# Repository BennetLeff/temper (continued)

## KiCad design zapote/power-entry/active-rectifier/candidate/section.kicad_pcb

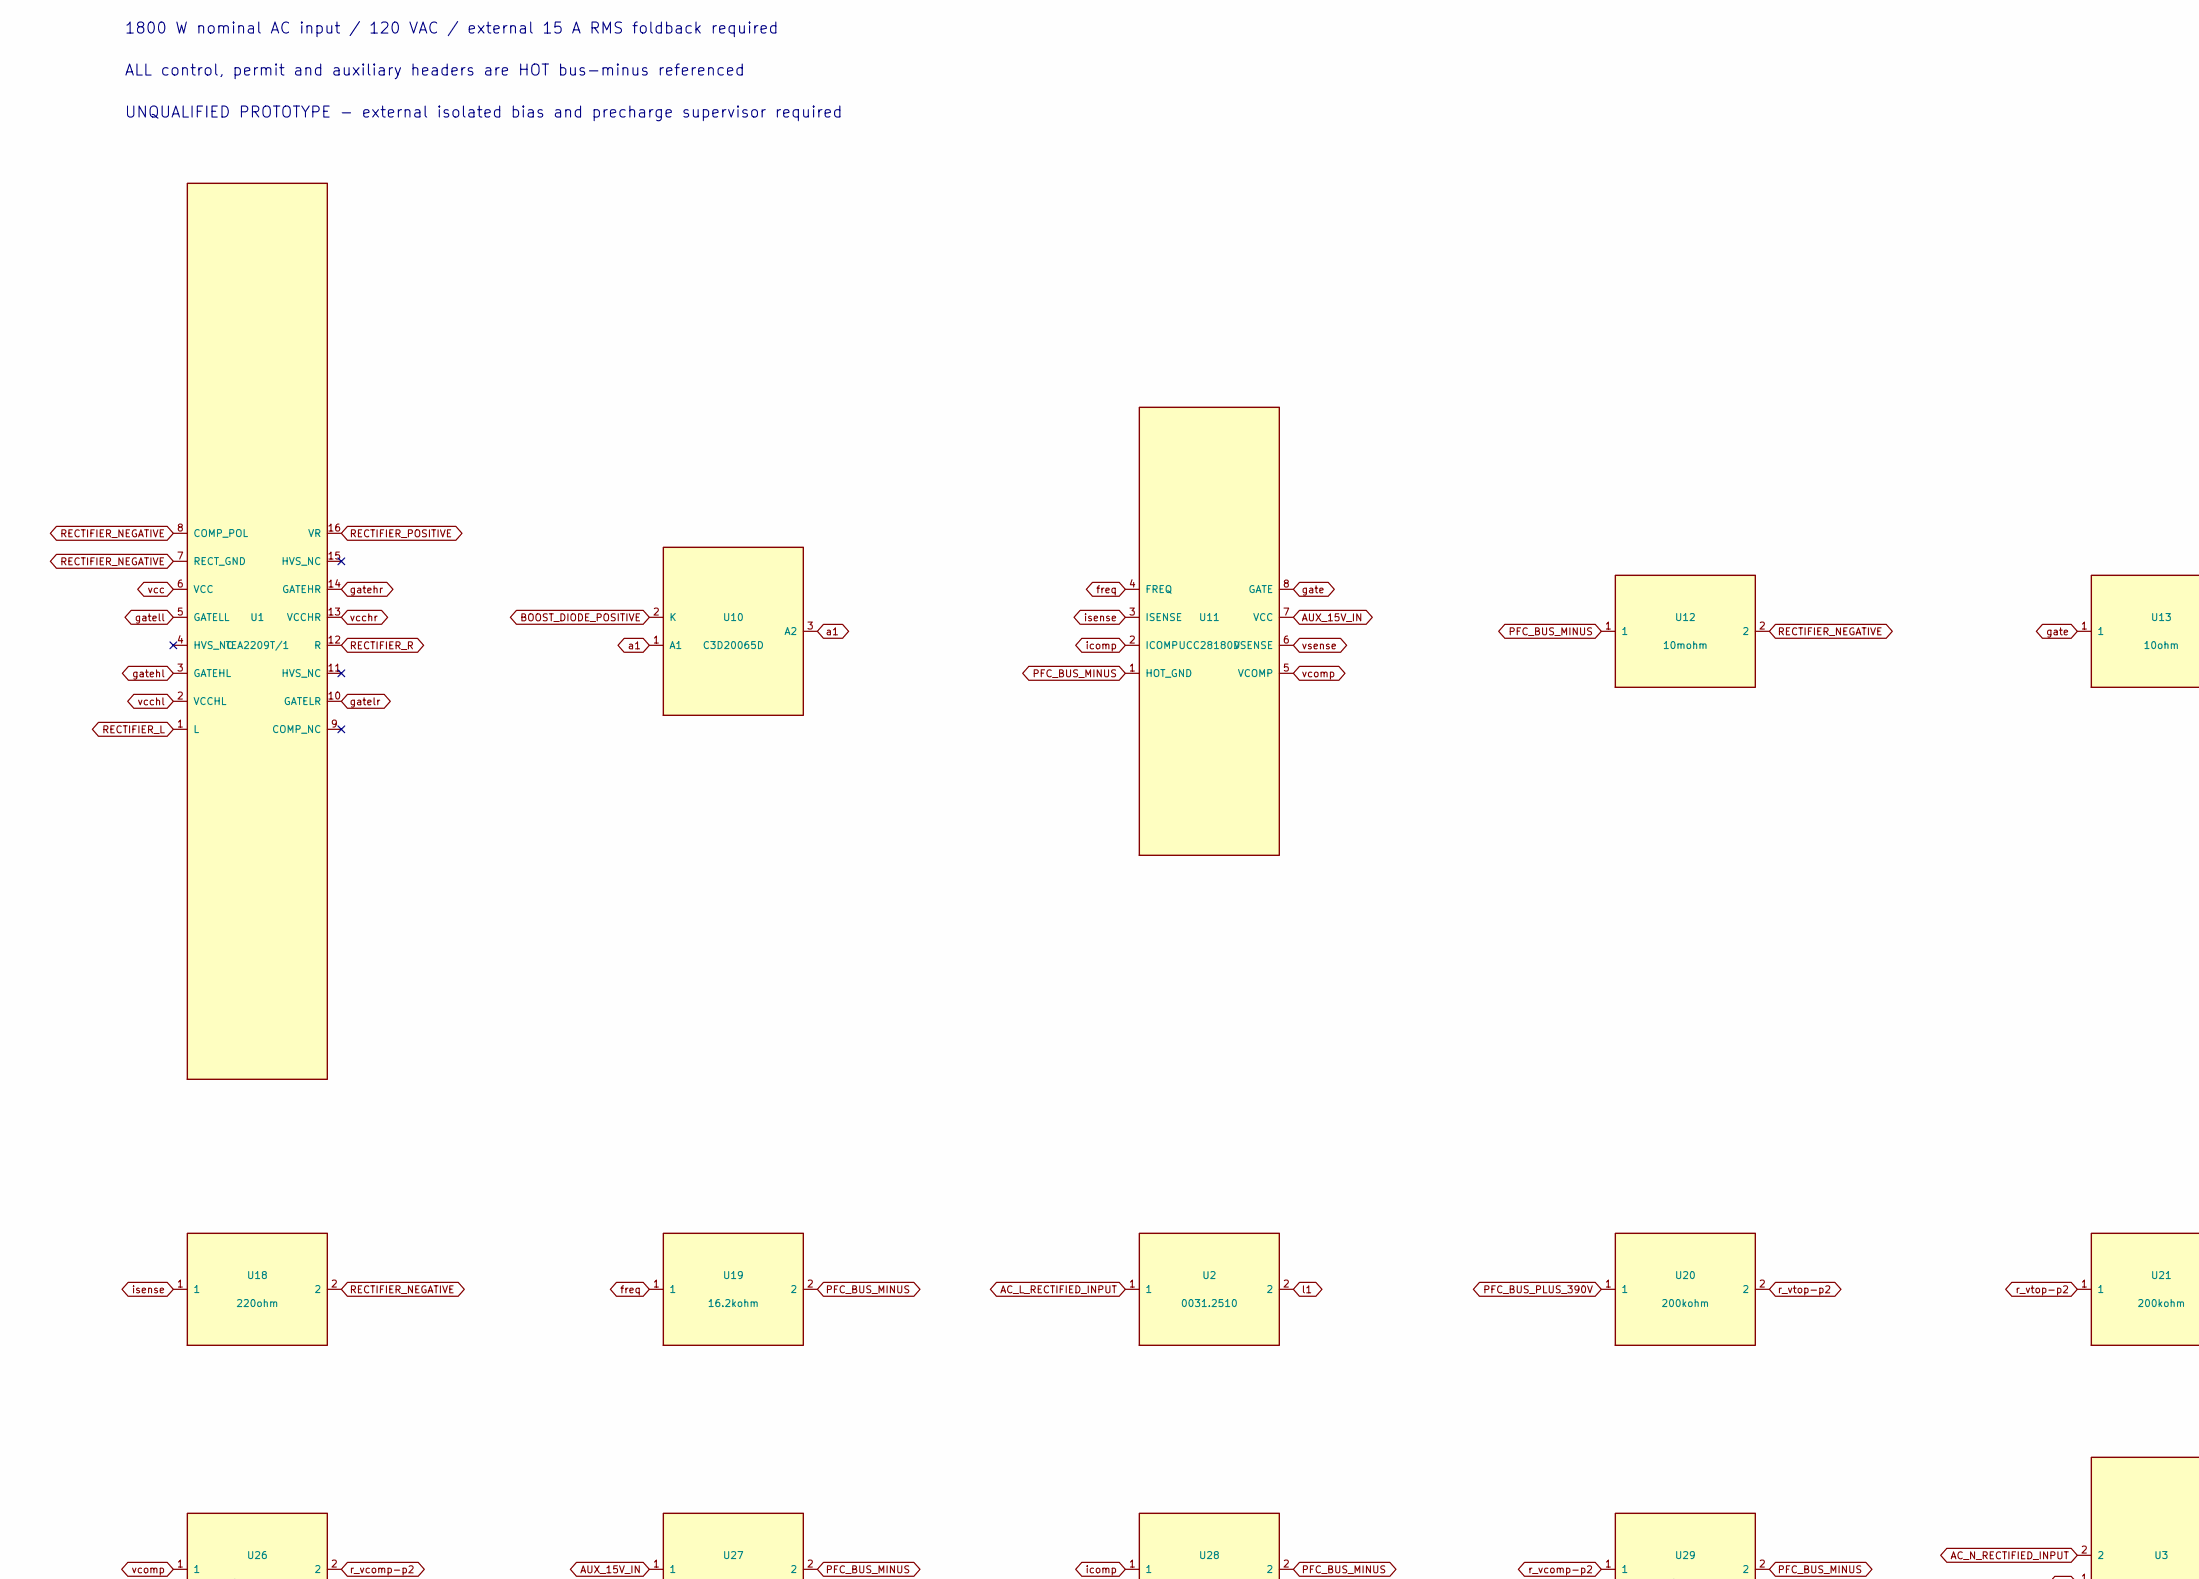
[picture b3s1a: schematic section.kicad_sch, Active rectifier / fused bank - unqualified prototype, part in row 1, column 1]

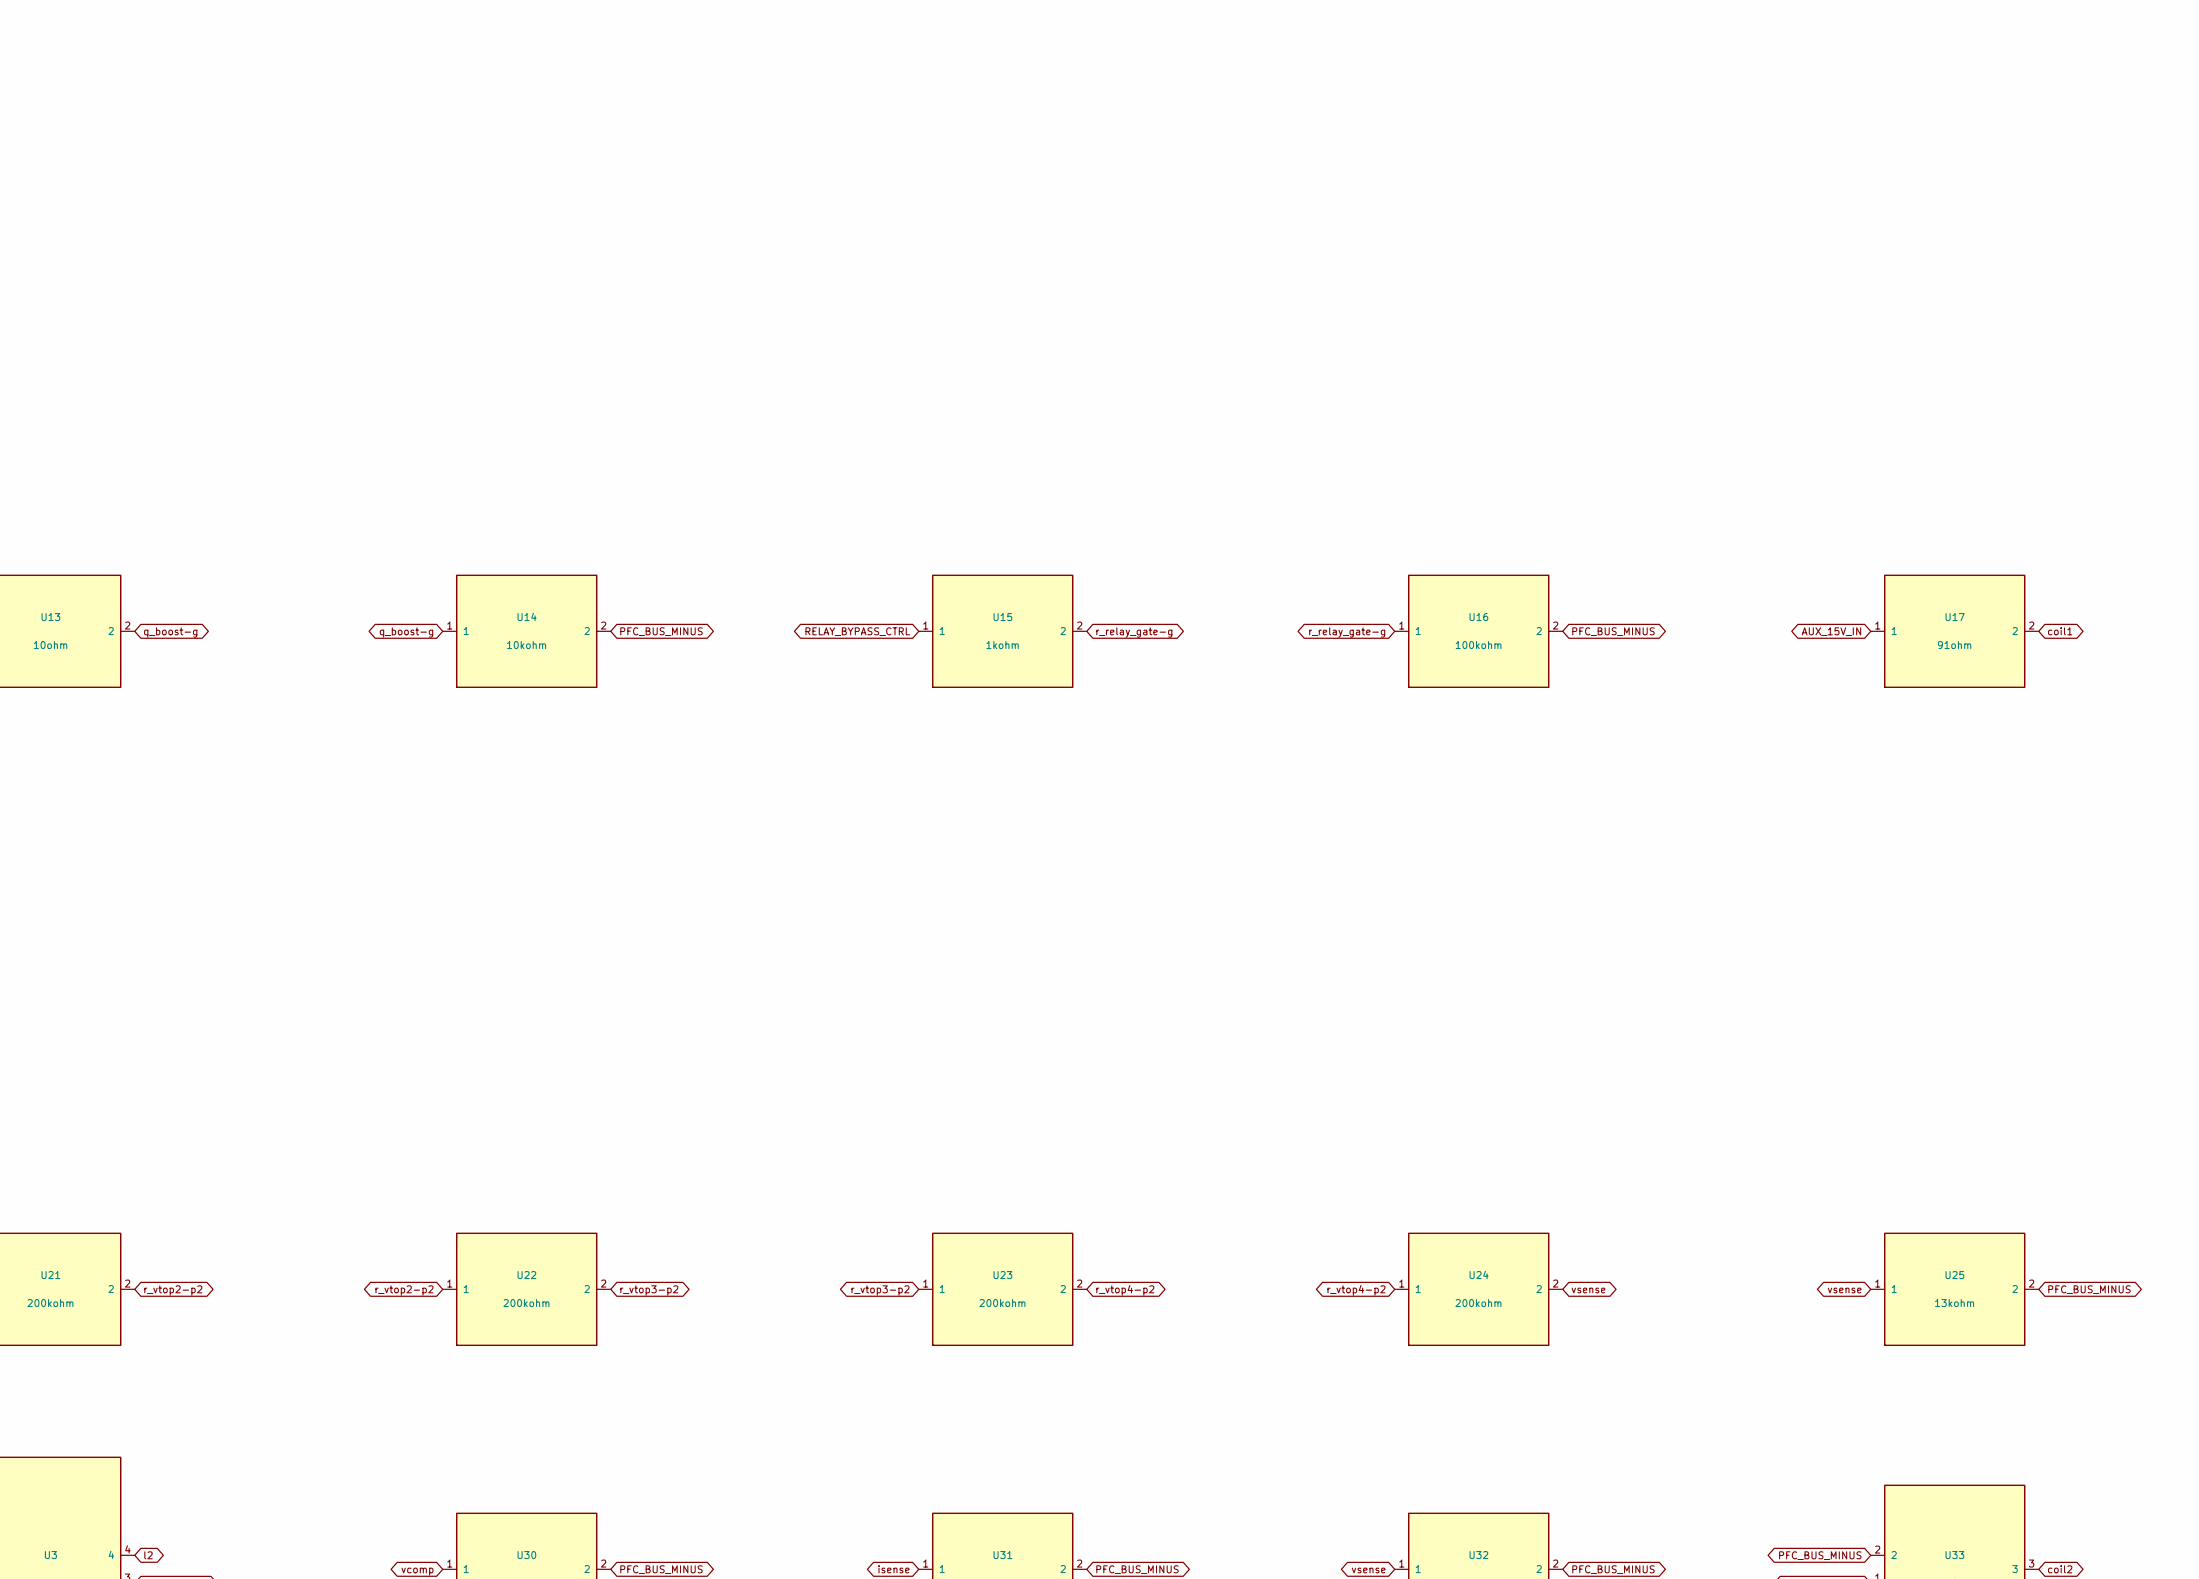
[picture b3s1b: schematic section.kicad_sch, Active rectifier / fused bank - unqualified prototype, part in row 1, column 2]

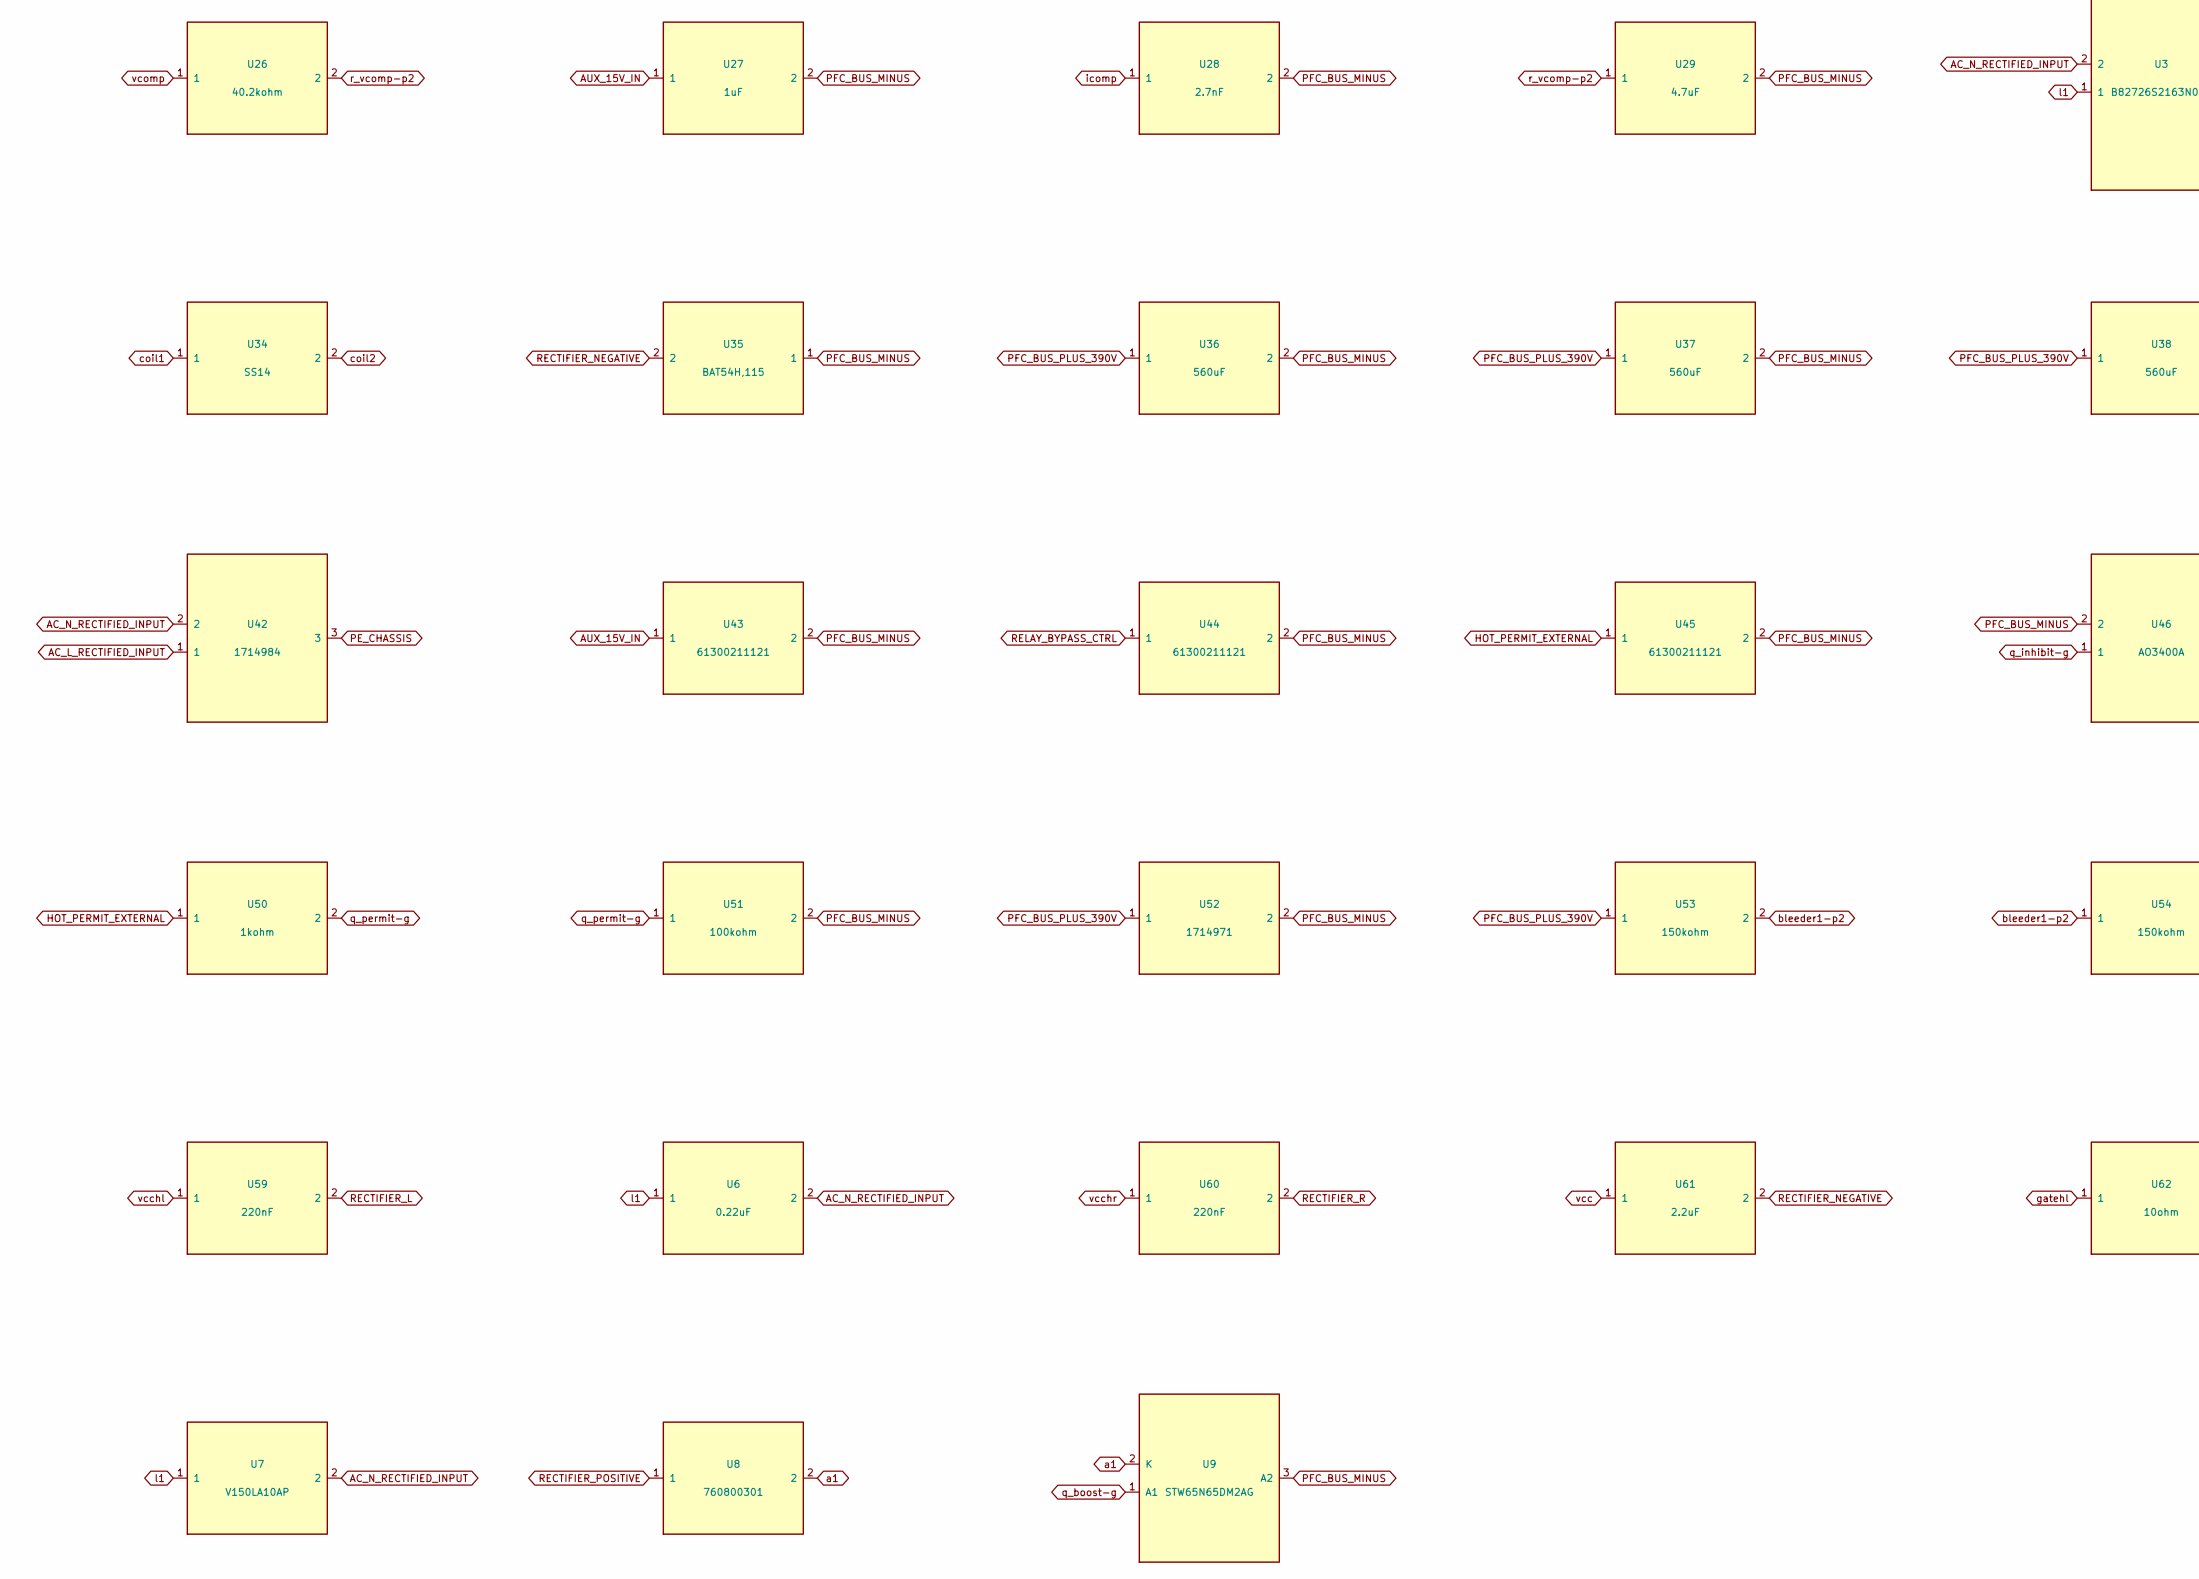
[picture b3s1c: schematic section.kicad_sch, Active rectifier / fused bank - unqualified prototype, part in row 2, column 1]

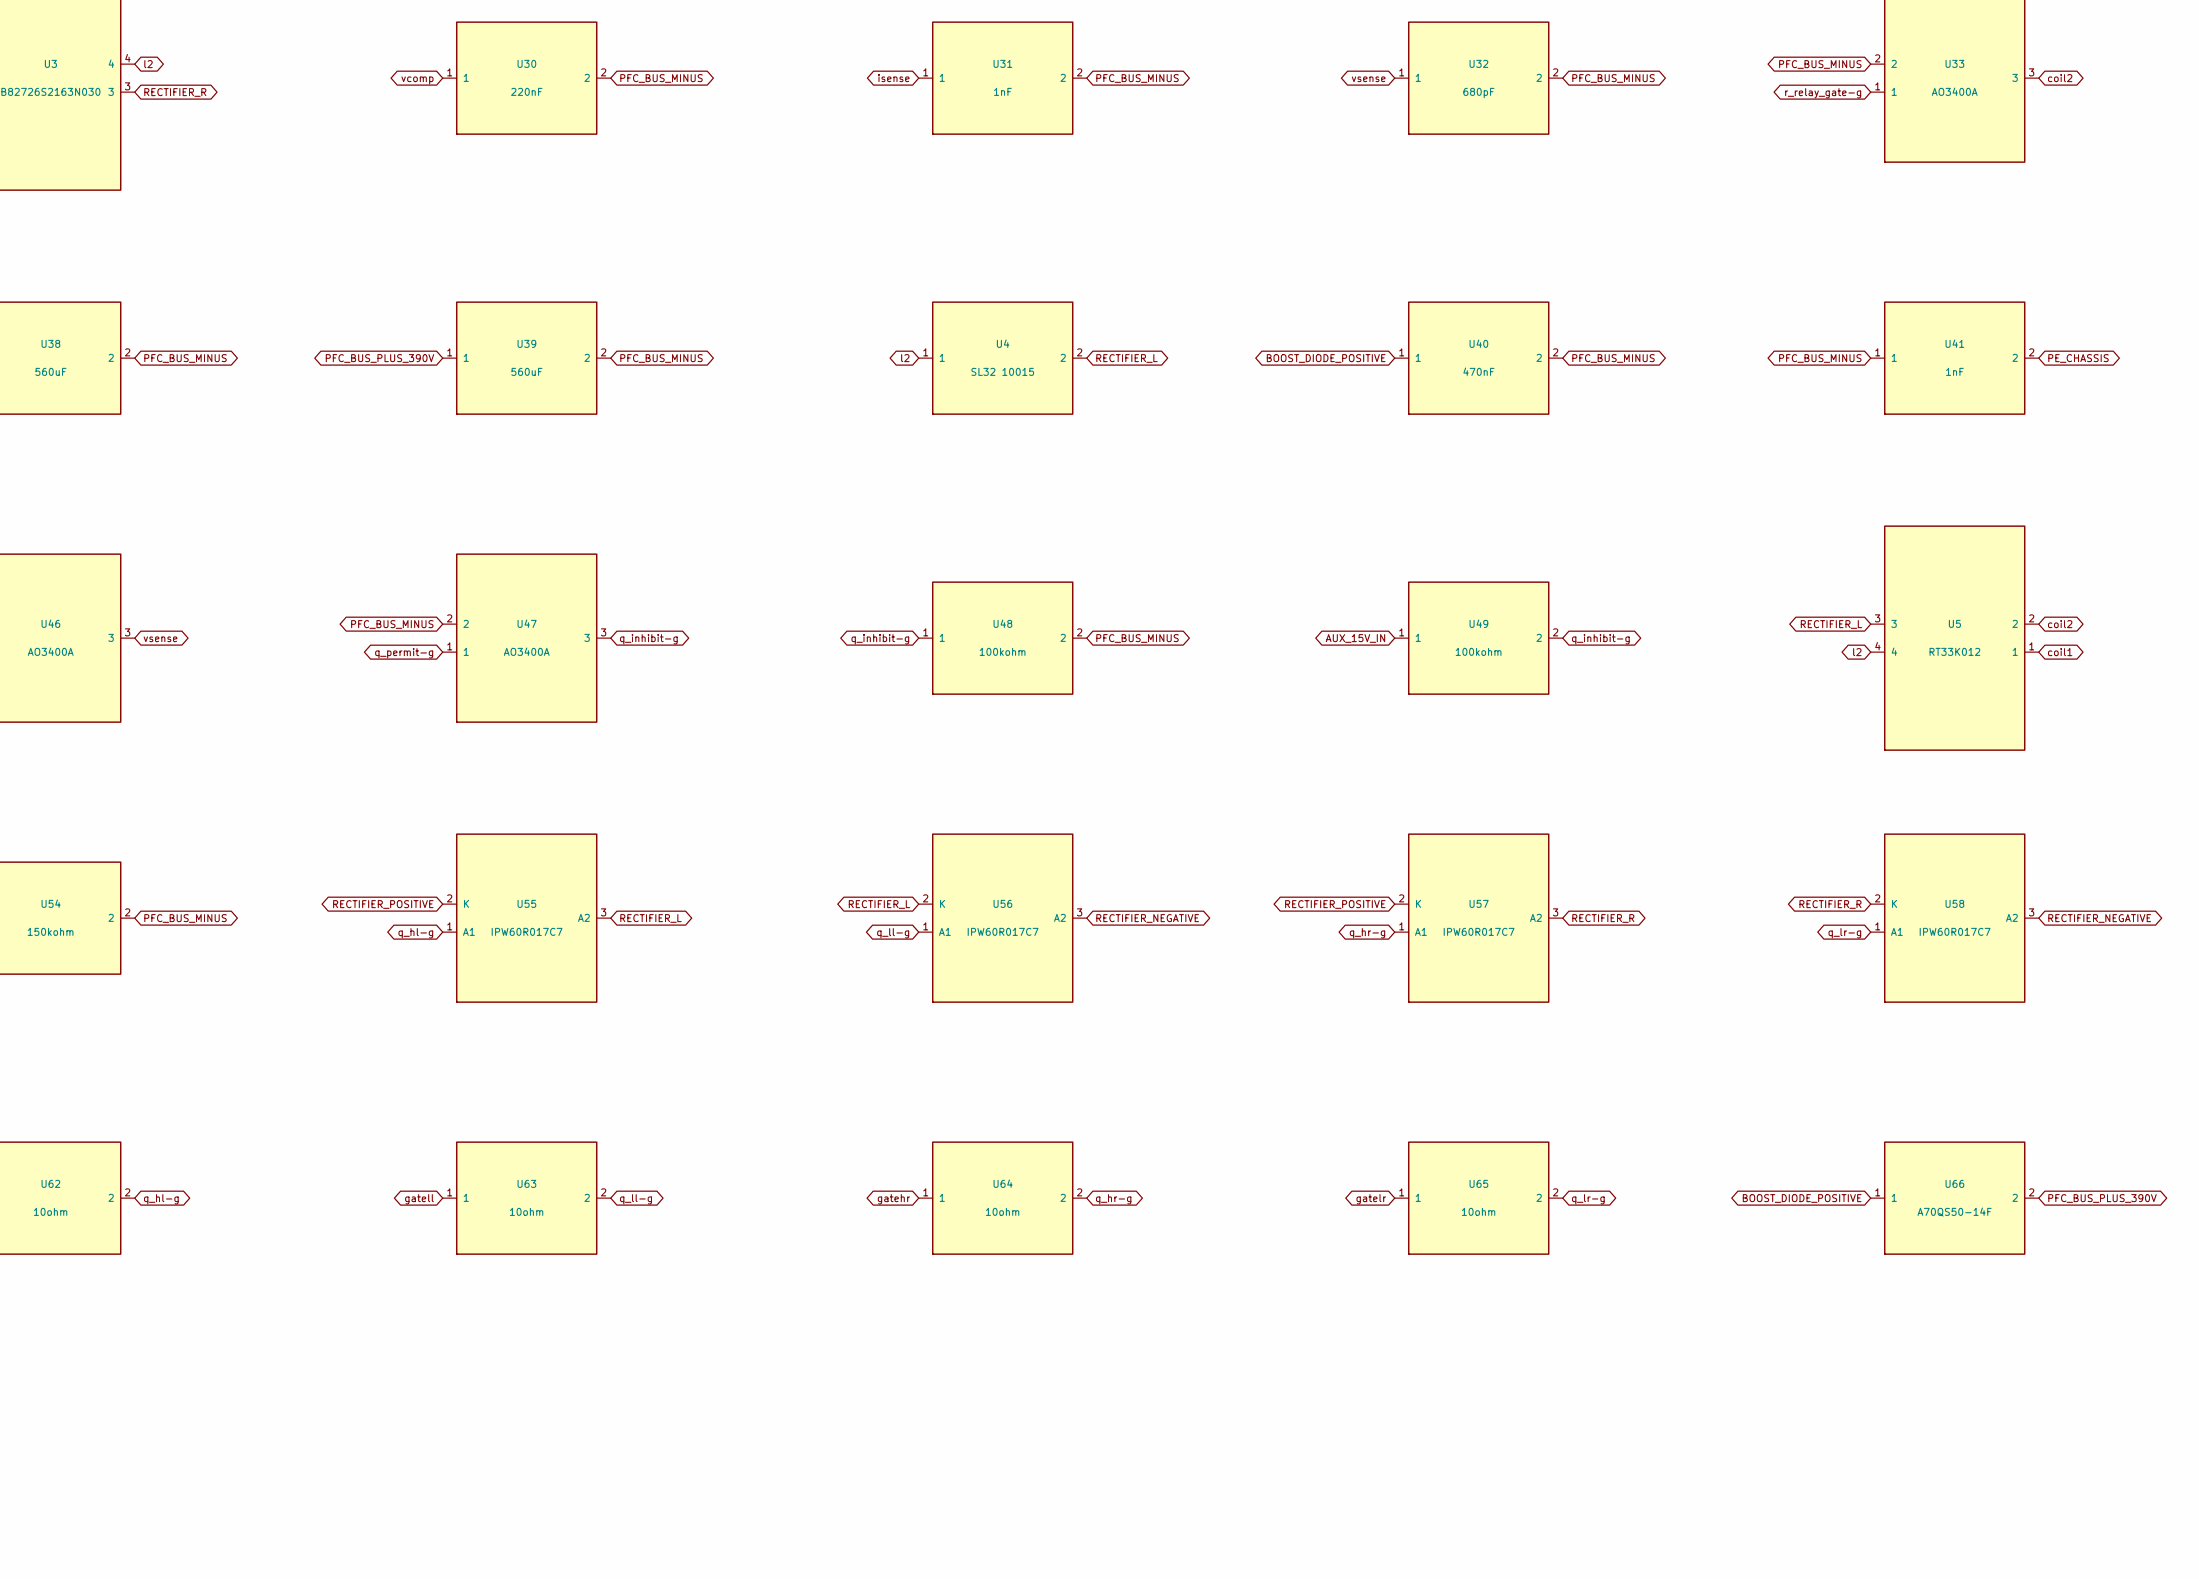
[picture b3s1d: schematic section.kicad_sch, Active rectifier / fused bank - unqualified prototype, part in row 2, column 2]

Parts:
U1: TEA2209T/1; SOIC-16_3.9x9.9mm_P1.27mm; MPN TEA2209T/1
U2: 0031.2510; Fuseholder_Cylinder-5x20mm_Schurter_FUP_0031.2510_Horizonta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; MPN 0031.2510
U3: B82726S2163N030; CMC_B82726S; MPN B82726S2163N030
U4: SL32 10015; SL32_10015; MPN SL32 10015
U5: RT33K012; Relay_SPST_Schrack-RT33K012; MPN RT33K012
U6: 0.22uF; C_Rect_L18.0mm_W7.0mm_P15.00mm_FKS3_FKP3; MPN B32922C3224M289
U7: V150LA10AP; RV_Disc_D15.5mm_W5.2mm_P7.5mm; MPN V150LA10AP
U8: 760800301; L_Wurth_WE-TORPFC-T75; MPN 760800301
U9: STW65N65DM2AG; TO-247-3_Vertical; MPN STW65N65DM2AG
U10: C3D20065D; TO-247-3_Vertical; MPN C3D20065D
U11: UCC28180D; SOIC-8_3.9x4.9mm_P1.27mm; MPN UCC28180D
U12: 10mohm; HCSM2818FT10L0; MPN HCSM2818FT10L0
U13, U62, U63, U64, U65: 10ohm; R_1206_3216Metric; MPN RC1206FR-0710RL
U14: 10kohm; R_1206_3216Metric; MPN RC1206FR-0710KL
U15, U50: 1kohm; R_1206_3216Metric; MPN RC1206FR-071KL
U16, U48, U49, U51: 100kohm; R_1206_3216Metric; MPN RC1206FR-07100KL
U17: 91ohm; R_2512_6332Metric; MPN RC2512FR-0791RL
U18: 220ohm; R_1206_3216Metric; MPN RC1206FR-07220RL
U19: 16.2kohm; R_1206_3216Metric; MPN RC1206FR-0716K2L
U20, U21, U22, U23, U24: 200kohm; R_2512_6332Metric; MPN CRCW2512200KFKEG
U25: 13kohm; R_1206_3216Metric; MPN RC1206FR-0713KL
U26: 40.2kohm; R_1206_3216Metric; MPN RC1206FR-0740K2L
U27: 1uF; C_0805_2012Metric; MPN C0805C105K5RACTU
U28: 2.7nF; C_0805_2012Metric; MPN C0805C272J5GACTU
U29: 4.7uF; C_1210_3225Metric; MPN GRM32ER71H475KA88L
U30, U59, U60: 220nF; C_0805_2012Metric; MPN C0805C224K5RACTU
U31: 1nF; C_0805_2012Metric; MPN C0805C102J5GACTU
U32: 680pF; C_0805_2012Metric; MPN C0805C681J5GACTU
U33, U46, U47: AO3400A; SOT-23; MPN AO3400A
U34: SS14; D_SMA; MPN SS14
U35: BAT54H,115; D_SOD-123F; MPN BAT54H,115
U36, U37, U38, U39: 560uF; CP_Radial_D35.0mm_P10.00mm_SnapIn; MPN LGX2W561MELC50
U40: 470nF; B32672P6474K000; MPN B32672P6474K000
U41: 1nF; C_Disc_Vishay_VY1102M31Y5UQ63V0; MPN VY1102M31Y5UQ63V0
U42: 1714984; Phoenix_1714984; MPN 1714984
U43, U44, U45: 61300211121; PinHeader_1x02_P2.54mm_Vertical; MPN 61300211121
U52: 1714971; Phoenix_1714971; MPN 1714971
U53, U54: 150kohm; R_2512_6332Metric; MPN RC2512FR-07150KL
U55, U56, U57, U58: IPW60R017C7; TO-247-3_Vertical; MPN IPW60R017C7
U61: 2.2uF; C_0805_2012Metric; MPN C0805C225K5RACTU
U66: A70QS50-14F; A70QS50_ETI_CH14_Prototype; MPN A70QS50-14F

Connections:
AC_L_RECTIFIED_INPUT: U2.1, U42.1
AC_N_RECTIFIED_INPUT: U3.2, U6.2, U7.2, U42.2
AUX_15V_IN: U11.7 (VCC), U17.1, U27.1, U43.1, U49.1
HOT_PERMIT_EXTERNAL: U45.1, U50.1
PE_CHASSIS: U41.2, U42.3
PFC_BUS_MINUS: U9.3 (A2), U11.1 (HOT_GND), U12.1, U14.2, U16.2, U19.2, U25.2, U27.2, U28.2, U29.2, U30.2, U31.2, U32.2, U33.2, U35.1, U36.2, U37.2, U38.2, U39.2, U40.2, U41.1, U43.2, U44.2, U45.2, U46.2, U47.2, U48.2, U51.2, U52.2, U54.2
RECTIFIER_L: U1.1 (L), U4.2, U5.3, U55.3 (A2), U56.2 (K), U59.2
RECTIFIER_NEGATIVE: U1.7 (RECT_GND), U1.8 (COMP_POL), U12.2, U18.2, U35.2, U56.3 (A2), U58.3 (A2), U61.2
RECTIFIER_POSITIVE: U1.16 (VR), U8.1, U55.2 (K), U57.2 (K)
RECTIFIER_R: U1.12 (R), U3.3, U57.3 (A2), U58.2 (K), U60.2
RELAY_BYPASS_CTRL: U15.1, U44.1
a1: U8.2, U9.2 (K), U10.1 (A1), U10.3 (A2)
bleeder1-p2: U53.2, U54.1
coil1: U5.1, U17.2, U34.1
coil2: U5.2, U33.3, U34.2
freq: U11.4 (FREQ), U19.1
gate: U11.8 (GATE), U13.1
gatehl: U1.3 (GATEHL), U62.1
gatehr: U1.14 (GATEHR), U64.1
gatell: U1.5 (GATELL), U63.1
gatelr: U1.10 (GATELR), U65.1
icomp: U11.2 (ICOMP), U28.1
isense: U11.3 (ISENSE), U18.1, U31.1
l1: U2.2, U3.1, U6.1, U7.1
l2: U3.4, U4.1, U5.4
q_boost-g: U9.1 (A1), U13.2, U14.1
q_hl-g: U55.1 (A1), U62.2
q_hr-g: U57.1 (A1), U64.2
q_inhibit-g: U46.1, U47.3, U48.1, U49.2
q_ll-g: U56.1 (A1), U63.2
q_lr-g: U58.1 (A1), U65.2
q_permit-g: U47.1, U50.2, U51.1
r_relay_gate-g: U15.2, U16.1, U33.1
r_vcomp-p2: U26.2, U29.1
r_vtop2-p2: U21.2, U22.1
r_vtop3-p2: U22.2, U23.1
r_vtop4-p2: U23.2, U24.1
r_vtop-p2: U20.2, U21.1
vcc: U1.6 (VCC), U61.1
vcchl: U1.2 (VCCHL), U59.1
vcchr: U1.13 (VCCHR), U60.1
vcomp: U11.5 (VCOMP), U26.1, U30.1
vsense: U11.6 (VSENSE), U24.2, U25.1, U32.1, U46.3

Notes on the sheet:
1800 W nominal AC input / 120 VAC / external 15 A RMS foldback required
ALL control, permit and auxiliary headers are HOT bus-minus referenced
UNQUALIFIED PROTOTYPE - external isolated bias and precharge supervisor required

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
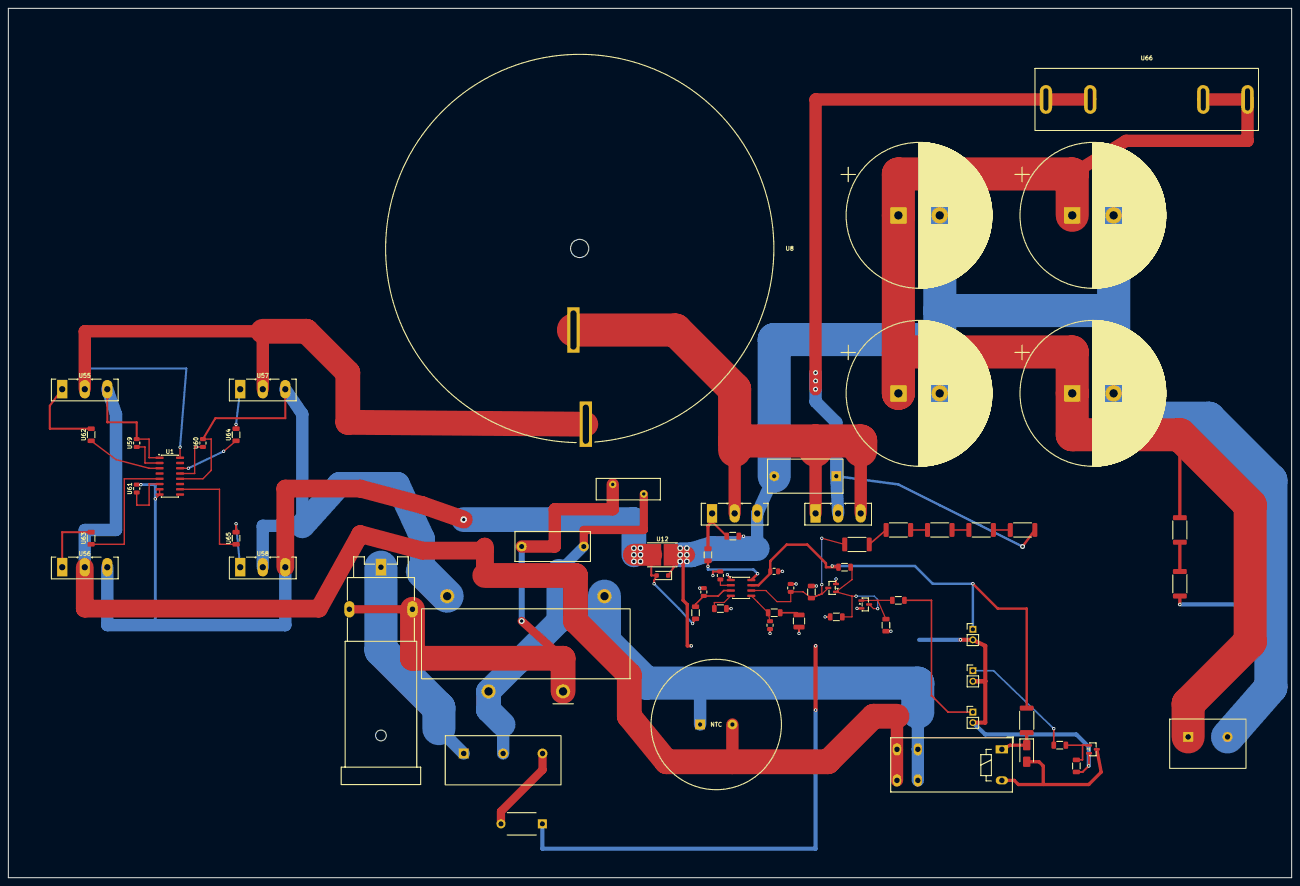
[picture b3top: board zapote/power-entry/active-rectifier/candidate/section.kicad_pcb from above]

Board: 2 copper layers, 310.0 x 210.0 mm, 66 parts (0 on the bottom side), 45 nets.
